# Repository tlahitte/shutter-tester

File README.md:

# Shutter Tester

> **Rev B (this fork).** A redesign that arrives fully assembled from JLCPCB with no
> soldering: a sensor board (ESP32-C6, three photodiodes, USB-C) and a separate light
> board. One set of both boards is roughly £70 to £85 delivered to the UK. Design,
> cost breakdown and ordering steps are in [hardware/README.md](hardware/README.md),
> firmware in [firmware/shutter-tester-revb](firmware/shutter-tester-revb). Not yet built
> or tested on hardware. The web UI also includes the USB (Web Serial) connection from
> [9vvin's fork](https://github.com/9vvin/shutter-tester) and the theming, error
> reporting and list fixes from [MichalTorma's fork](https://github.com/MichalTorma/shutter-tester).
> Everything below is Ben Pirt's original README for the original
> board, which this work is based on.

A low cost but capable three-point shutter speed tester that runs on ESP32. It uses the PCB design to provide the physical structure of the tester so that all you need to do is solder it together and all of the mechanical design is taken care of.
It runs on ESP32 so is easily updated using the Arduino platform. The project is 100% open source (see the [license file](LICENSE.md) for details).
The UI runs in the browser and communicates with the shutter tester via Bluetooth - you can try out the UI [here](https://bjpirt.github.io/shutter-tester/?demo=true).

## Design

The design of the shutter tester is quite simple; it uses three IS485E / IS486E light sensors with built-in amplifiers to trigger three digital input interrupts on the ESP32 MCU. I wanted to keep the front side of the PCB clear to avoid it ever scratching the camera body so have opted for using surface mount components. I've used quite large packages for these so that they can be more easily hand soldered. The ESP32 uses an "ESP32 C3 Super Mini" module which is very small, can be surface mounted and has USB C built-in which can be used to power the whole board. I've kept the PCB size down to 50mm so that you can take advantage of low cost PCB fabrication. There are silk-screen markings to help position the tester over the camera shutter and three large holes to help see the edges from behind. It should either be taped in place or held with an elastic band.

The sensor has a Bluetooth connection and you can connect this to Chrome to use quite a capable web interface so you can get a lot of detail on the calibration. You can try out the UI [here](https://bjpirt.github.io/shutter-tester/?demo=true)

## Bill of materials

The BoM is quite low cost and relatively minimal:

- 1 x ESP32 C3 Super Mini module
- 3 x IS485E light sensor
- 6 x 1k 1206 SMD Resistor
- 3 x 2k 1206 SMD Resistor
- 3 x 0.01uF 1206 SMD Capacitor

## Assembly

The main thing to take care over during assembly is to ensure the lens of the light sensor aligns to the small hole in the PCB that allows the light through. The three legs of the sensor should be bent down slightly so that they can solder onto the three pads on the PCB.

The capacitors and resistors can be easily hand soldered (a finer soldering iron tip helps here) by applying solder to one of the pads on the PCB, using tweezers, solder one end of the component to the soldered pad on the PCB, then solder the other end once it is held in place. If you're experienced in surface mounting you could always use solder paste, but it's pretty straightforward without this. There are markings on the board for which component goes where (C1, C2 and C3 for the capacitors, Resistor values are marked 1k and 2k). The capacitors are optional and may be removed in a future iteration.

It's best to test the ESP32 module before soldering to ensure it's working fine. Program this using the sketch included and make sure it is outputting "Ready to measure" on the serial console (running at 921600 baud).

It's a good idea to place some black insulation tape over the back of the sensors otherwise stray light can cause false readings.

## Usage

Attach the shutter tester behind the shutter of the camera (I normally use 2 - 3 small blobs of Blu-Tak which works well). You can use the three larger holes in the tester to align with the edges of the shutter aperture. Open the shutter once you've this so you can check it's properly positioned by setting the shutter to "Bulb" and opening it. Remove the lens (if possible) and place a strong, even light at the front of the camera. You can use a full size bulb for this so long as it is the type that has a white diffuser bulb, not clear. Basically you want to ensure that light can pass directly through the three holes to reach the sensors, not at an angle. I've also had good results with a small USB powered LED panel.

### Using Bluetooth

There is a user interface that connects to the ESP32 from a Chrome web browser directly and lets you analyse all of the measurements quite easily.

You can easily use the [latest version](https://bjpirt.github.io/shutter-tester/). You should then be able to click the `Connect` button and pair with your shutter tester using Bluetooth. Select the speed you want to test, set up the light and fire the shutter. The new reading should appear in the table.

If you want to just try out the UI without a tester, you can use [this link](https://bjpirt.github.io/shutter-tester/?demo=true) and the "Test" button will simulate a shutter being fired. From a privacy perspective, the UI runs entirely in your browser and nothing goes over the internet.

If you want to run this locally you can do the following:

- Install Node.js (v22)
- Open a terminal in the `ui` folder of this repository
- run `npm install`
- run `npm run dev`
- Go to the URL printed in your terminal ([http://localhost:5173/](http://localhost:5173/))

### Using serial

Open a serial terminal to the ESP32 (this is built in to the Arduino IDE). You'll need to connect at 921600 baud.

Fire the shutter and it will print out the timings to the serial console. There are two sets of timings:

- The time taken for each shutter to travel across the frame - it's important to try and get both shutters moving at around the same speed
- The time each sensor was exposed for in microseconds, milliseconds and fractions of a second

```
Ready to measure

Shutter timing
Shutter 1: 1-2: 16582 uS || 2-3: 12632 uS
Shutter 2: 1-2: 23756 uS || 2-3: 18462 uS

Exposure timing
Sensor 1: 4346 uS || 4.3 mS || 1 / 228
Sensor 2: 5028 uS || 5.0 mS || 1 / 198
Sensor 3: 5528 uS || 5.5 mS || 1 / 182
```

In this example, the time taken for the first shutter to travel between the first and second (centre) sensors was 16582 microseconds and 12632 microseconds between the second (centre) and third sensor. You can see that in this example the second shutter is slow and would need adjusting.

Looking at the exposure time at each sensor, you can see the timings would need adjusting to give a good even exposure. First you would adjust the shutter timings to try and get them similar and then adjust both shutter tensioners to get the exposure time to match the expected (in this case it should have been 1/250 S)

# To Do

- [ ] Calculate variations across shutter and whether they are within tolerances
- [ ] Add graph visualisation of shutter speeds
- [ ] Generate report from three point test
- [x] Enable detailed measurements to be shown / hidden in three point mode
- [x] Deploy to GitHub pages using GitHub actions
- [x] Automatically work out vertical or horizontal shutter
- [x] Display full shutter timing
- [x] Separate shutter timing mode
- [x] Single shot mode (only show last shot timing) - useful for initial tuning
- [x] Compensation for sensor width

## Future

- [ ] Add persistence in the browser to enable common presets to be stored - e.g. camera types with speeds
- [ ] Enable different "runs" to be stored and compared so you can see progression when adjusting
- [ ] Add exposure measurement with light to frequency sensor
- [ ] Investigate reflective measurement from front of camera for e.g. Barnack Leicas
- [ ] Investigate using an analog photodiode instead of a binary sensor

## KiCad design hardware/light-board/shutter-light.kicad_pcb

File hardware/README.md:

# Shutter tester rev B hardware

Derived from Ben Pirt's three-point shutter tester
(https://github.com/bjpirt/shutter-tester), hardware under CERN-OHL-P v2. The upstream
KiCad 8 board is still here as `shutter-tester.kicad_*` for reference.

Rev B is two 2-layer boards that arrive fully assembled: a 77 x 34 mm sensor board and a
50 x 50 mm light board. Nothing to solder.

| Board | Folder | What it does |
|-------|--------|--------------|
| Sensor | `sensor-board/` | Sits at the film plane. Three photodiodes on the frame diagonal, ESP32-C6, USB-C |
| Light | `light-board/` | Nine white LEDs, DC driven from any USB-C charger, goes in front of the lens |

## Sensor board

- 3 x Vishay VBPW34SR photodiodes mounted on the component side, each looking through a
  1.2 mm plated hole. The camera-facing side is flat with no parts on it.
- Each photodiode feeds a transimpedance amp (MCP6004, 1M, about 23 kHz bandwidth) and
  an LM339 comparator. The firmware sets each comparator threshold with a filtered PWM
  output, so calibration is automatic and there are no trimmers.
- ESP32-C6-WROOM-1-N8 timestamps comparator edges in hardware (MCPWM capture), so timing
  does not depend on interrupt latency.
- USB-C for power, flashing and serial. BOOT button for manual download mode if needed.
- The board is 34 mm tall so it drops into the film channel and lies on the film rails.
  The frame centre is 25 mm from the USB end, so the plug lies in the channel on one
  side of the gate. The electronics reach 52 mm the other way and sit over the cassette
  chamber. That fits the film cavity of a normal 35 mm SLR or rangefinder; it is too long
  for a compact, where it has to be held against the back instead.
- Sensor positions on the board: (9,7), (25,17), (41,27) mm. Silk on the camera side
  shows the 36 x 24 mm frame outline.

## Light board

9 LEDs at about 21 mA each, straight from USB 5 V through 100R. No PWM anywhere, so the
light has no flicker that could be read as a shutter edge. Four 3.2 mm mounting holes.
If the sensor board reports saturation, move the light further away.

## Light levels

Estimates only, nothing measured. A photodiode behind a 1.2 mm aperture gives roughly
1.3 mV per lux of white LED light at the amplifier output, and the output clips at about
1.6 V. With the light board held against the front of the lens that works out to:

| Lens setting | Centre sensor | Corner sensors |
|--------------|--------------:|---------------:|
| f/2          | clips, move the light back | about 1 V |
| f/2.8        | about 1.2 V   | about 0.5 V |
| f/5.6        | about 0.3 V   | about 0.12 V |
| f/8          | about 0.15 V  | about 0.06 V |

So test with the lens between f/2.8 and f/8. Calibration needs at least 30 mV between dark
and lit and warns below 60 mV. With the lens off, start with the light 20 cm away. If the
firmware reports saturation, move the light back; if it reports too dim, open the lens up.

## Regenerating

The KiCad files are generated. Change the Python, not the KiCad files.

    . scripts/_env.sh sensor-board
    (cd hardware/gen && "$KICAD_PY" sensor_board.py)    # or light_board.py
    scripts/check.sh sensor-board                       # ERC + DRC, must be clean
    scripts/render.sh sensor-board front                # PNG in fab/sensor-board/
    scripts/fab.sh sensor-board                         # fab/sensor-board/jlcpcb/

`fab.sh` ends by running `scripts/cplcheck.py`. It downloads JLCPCB's own footprint for
every LCSC part on the BOM, lays it on the board at the position and rotation written in
`cpl.csv`, and fails if a pad misses or a diode or IC ends up the wrong way round. The
rotation and origin corrections it checks live in the `FIX` table in `fab.sh`.

## Estimated cost

Estimate from 16 Nov 2026, in USD because that is what JLCPCB quotes in. Part prices are
live JLCPCB prices on that date. The fees are JLCPCB's usual economic assembly fees and
are not taken from a real quote, so treat the totals as a guide and check the quote page.

| Per order | Sensor board | Light board |
|-----------|-------------:|------------:|
| 5 bare PCBs (minimum) | $2 | $2 |
| Assembly setup + stencil | $9.50 | $9.50 |
| Extended parts fee ($3 per part type) | $15 (5 types) | $6 (2 types) |
| Parts, per assembled board | $7.30 | $0.34 |
| **Total, 2 boards assembled** | **about $42** | **about $19** |
| **Total, 5 boards assembled** | **about $64** | **about $20** |

One working set (2 of each, the minimum JLCPCB will assemble) comes to about $60 before
shipping. Add roughly $15 to $25 shipping to the UK and 20% VAT at checkout, so expect
somewhere around £70 to £85 delivered. Most of the cost is fixed fees, which is why a
single set is expensive per board and five sets are only about £100.

## Ordering at JLCPCB

Two separate orders, one per board. For each one:

1. jlcpcb.com, "Order now", upload `fab/<board>/jlcpcb/gerbers.zip`.
2. PCB options: 2 layers, 1.6 mm, qty 5, HASL lead-free. Black solder mask for the sensor
   board (less stray light), any colour for the light board. Leave the rest at default.
3. Turn on "PCB Assembly": Economic, Top side, qty 2 or 5, "Confirm parts placement" on.
4. Upload `bom.csv` and `cpl.csv`. Every part should match by LCSC number. If one is out
   of stock, stop and pick a substitute before going further.
5. In the placement preview, check before paying. `cplcheck.py` has already compared
   every placement with JLCPCB's footprints, so anything that looks wrong here is worth
   stopping for:
   - U2, U3 (SOIC-14): pin 1 dot matches the silk dot
   - U4 (SOT-223): tab on the wide pad
   - U1 (ESP32 module): antenna end at the board edge, over the bare area
   - J1 (USB-C): opening faces off the board and the two pegs sit in their holes
   - Sensor board LED1, LED2: cathode mark matches the silk
   - Light board D1 to D9: the large pad of the LED sits on the large board pad (the
     cathode, on the left)
   - D1 to D3 on the sensor board: body centred over the hole (either way round is fine,
     the circuit does not care about photodiode polarity)
6. Ship to the UK. Under £135, VAT is collected at checkout and there is nothing to pay
   on delivery.

## Not verified yet

- No board has been built. The front end gain is an estimate and the firmware has only
  been compiled, never run on hardware.
- The corrections written into `cpl.csv` (SOT-223 +180, SOIC +270, 2835 LED +180, USB-C
  origin moved 1.394 mm towards its pads) were worked out from JLCPCB's EasyEDA footprints
  for the exact parts and are checked by `cplcheck.py`. That assumes JLCPCB places parts the
  way its footprint is drawn, which is how it normally works but has not been confirmed
  with a real order, hence step 5.
- The photodiodes are clear packages on the open side of the board, so room light reaches
  them from behind, and the two 2.5 mm sighting holes let light straight through. Expect to
  need black tape over D1 to D3 and over both sighting holes, or a dim room.
- Fit in a real camera has not been tried. Cut a 77 x 34 mm piece of card, mark the frame
  centre 25 mm from one end, and check it lies on the film rails of your camera with room
  for a USB-C plug on the short end before ordering.
- VBPW34SR stock at JLCPCB was 925 on 16 Nov 2026. It dropped to 10 in June 2026 and was
  restocked within a month, so recheck before ordering. There is no drop-in alternative.
- Bluetooth range with the board against a metal camera body is unknown. The antenna is
  at the far end over the cassette chamber. If Bluetooth is weak, use the USB connection
  in the web UI.
- Black solder mask at 1.6 mm with HASL is listed by JLCPCB as an economic assembly
  option. If the order page refuses it, pick green and plan on the black tape below.
- The four USB shell legs have solder paste in their slots so they are reflowed with the
  other parts. If the placement preview or the delivered board shows them unsoldered, the
  connector is held by its pins only: support the cable and do not lever on the plug.
- Coupling from the USB data lines and comparator outputs into the 1M amplifier inputs is
  kept down by extra spacing, but is an estimate, not a measurement. If a channel shows
  spurious edges at very low light, use Bluetooth instead of USB for that test.
- No ESD protection or fuse on USB. Fine for a bench prototype.

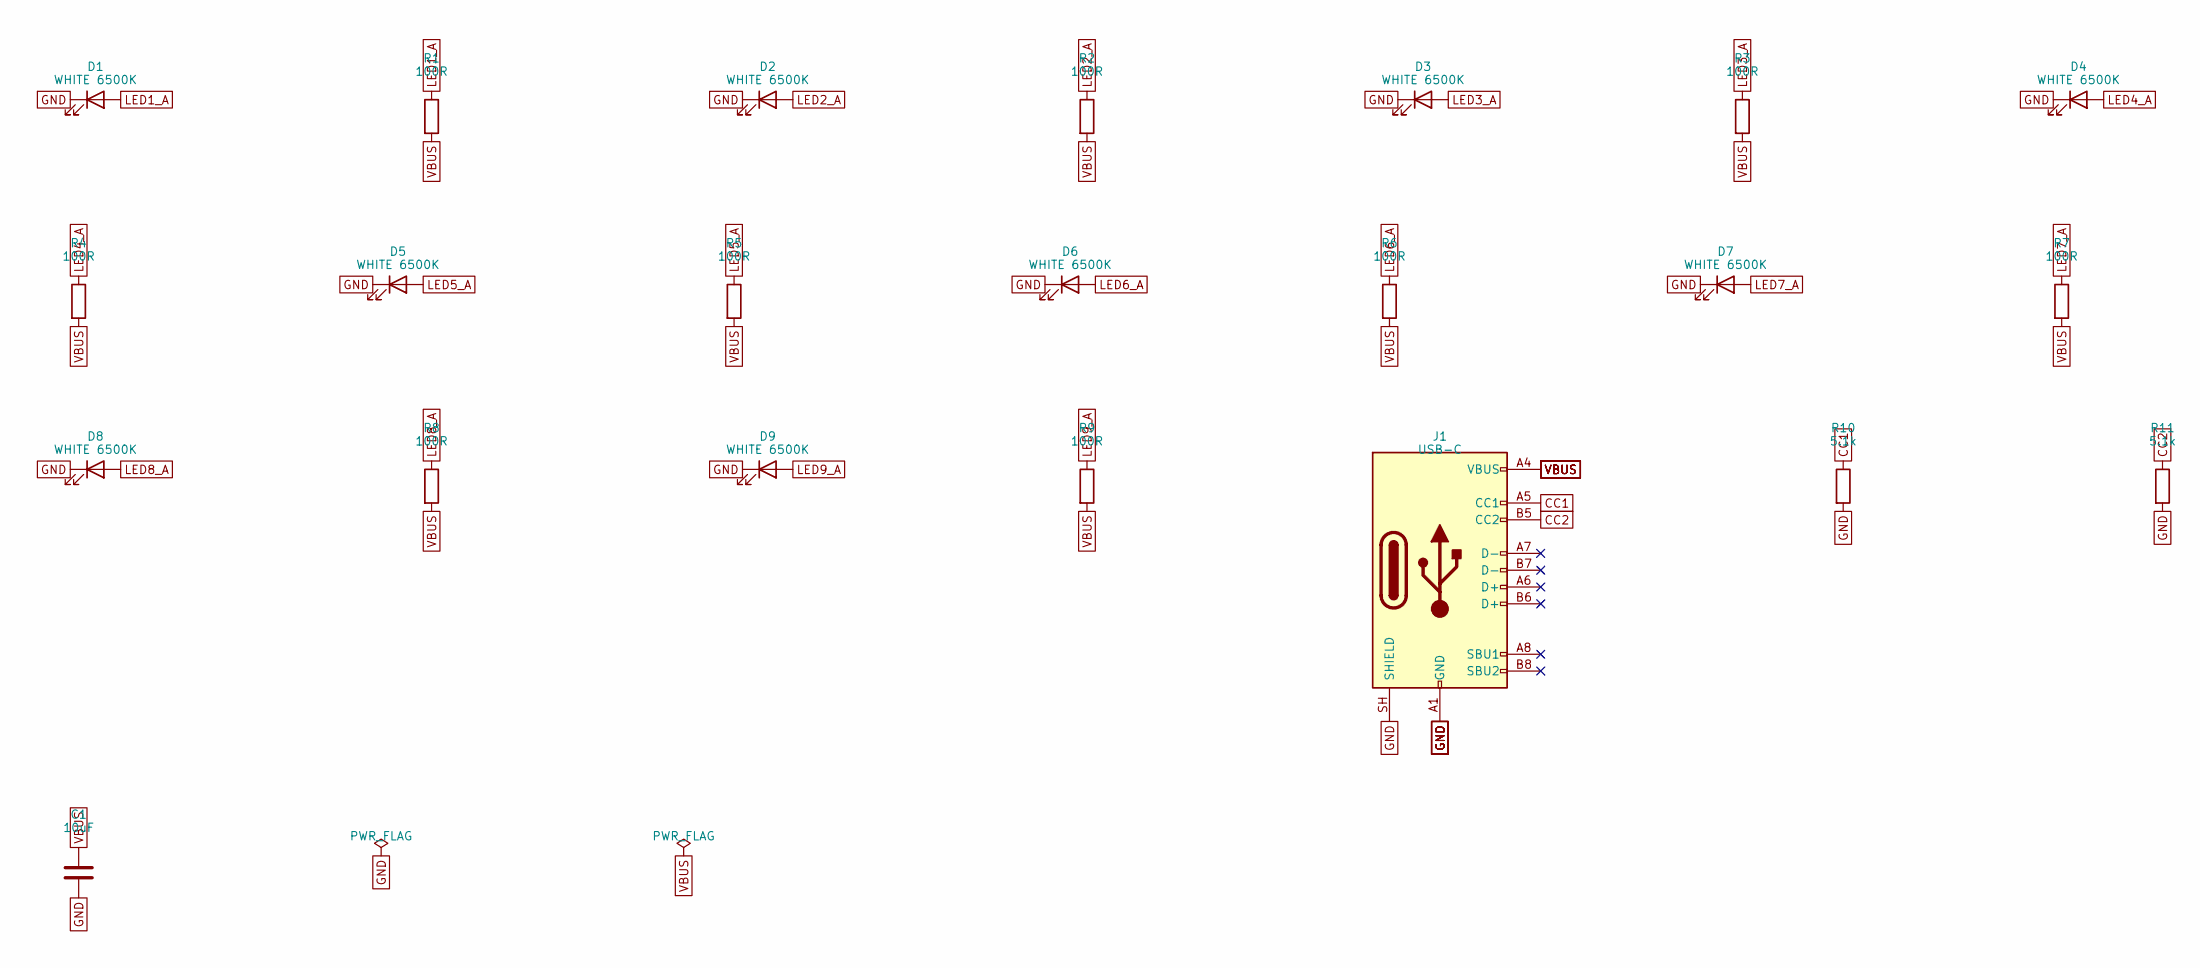
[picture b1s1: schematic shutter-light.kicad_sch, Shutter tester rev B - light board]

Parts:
C1: 10uF; C_0805_2012Metric; LCSC C15850
D1, D2, D3, D4, D5, D6, D7, D8, D9: WHITE 6500K; LED_PLCC_2835; MPN 67-21S/KK7C-H657034Z15/DT; LCSC C385305
J1: USB-C; USB_C_Receptacle_HRO_TYPE-C-31-M-12; MPN TYPE-C-31-M-12; LCSC C165948
R1, R2, R3, R4, R5, R6, R7, R8, R9: 100R; R_0805_2012Metric; LCSC C17408
R10, R11: 5.1k; R_0402_1005Metric; LCSC C25905

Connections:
CC1: J1.A5 (CC1), R10.1
CC2: J1.B5 (CC2), R11.1
GND: C1.2, D1.1 (K), D2.1 (K), D3.1 (K), D4.1 (K), D5.1 (K), D6.1 (K), D7.1 (K), D8.1 (K), D9.1 (K), J1.A1 (GND), J1.A12 (GND), J1.B1 (GND), J1.B12 (GND), J1.SH (SHIELD), R10.2, R11.2
LED1_A: D1.2 (A), R1.1
LED2_A: D2.2 (A), R2.1
LED3_A: D3.2 (A), R3.1
LED4_A: D4.2 (A), R4.1
LED5_A: D5.2 (A), R5.1
LED6_A: D6.2 (A), R6.1
LED7_A: D7.2 (A), R7.1
LED8_A: D8.2 (A), R8.1
LED9_A: D9.2 (A), R9.1
VBUS: C1.1, J1.A4 (VBUS), J1.A9 (VBUS), J1.B4 (VBUS), J1.B9 (VBUS), R1.2, R2.2, R3.2, R4.2, R5.2, R6.2, R7.2, R8.2, R9.2

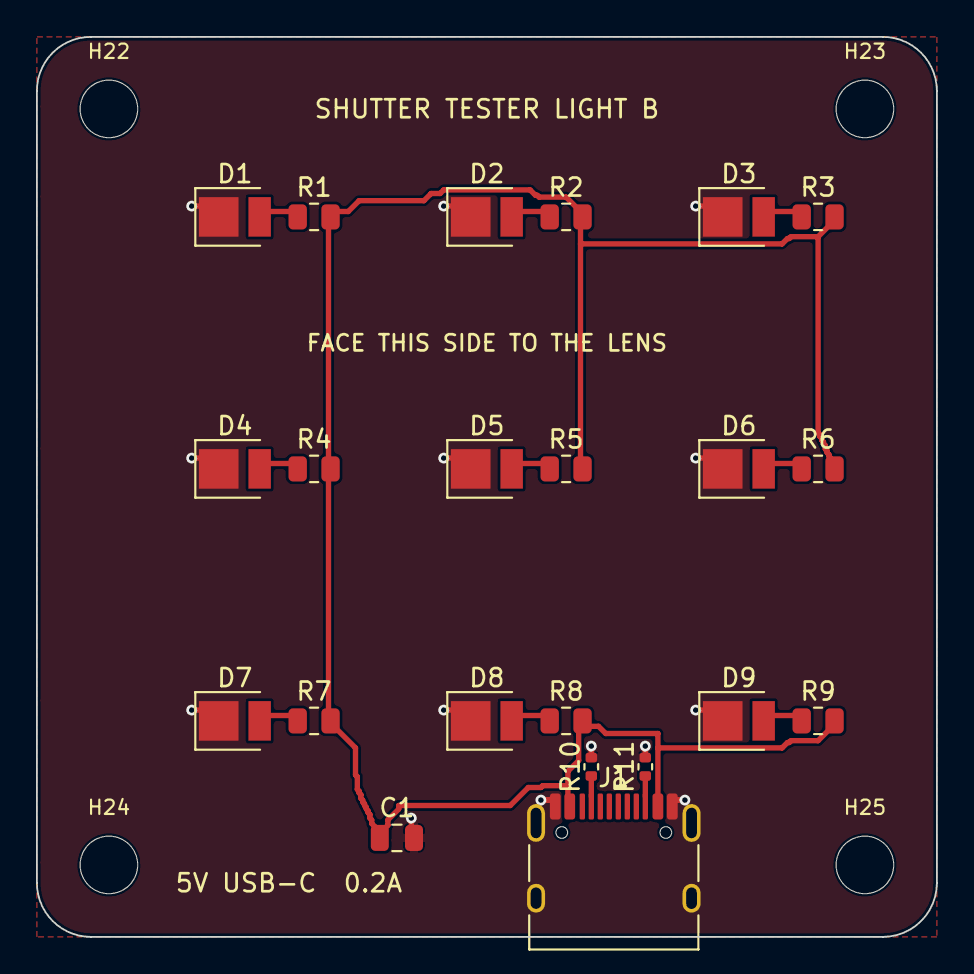
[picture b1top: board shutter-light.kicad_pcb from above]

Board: 2 copper layers, 50.0 x 50.0 mm, 26 parts (0 on the bottom side), 13 nets.

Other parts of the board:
H22, H23, H24, H25: NPTH_3.2mm

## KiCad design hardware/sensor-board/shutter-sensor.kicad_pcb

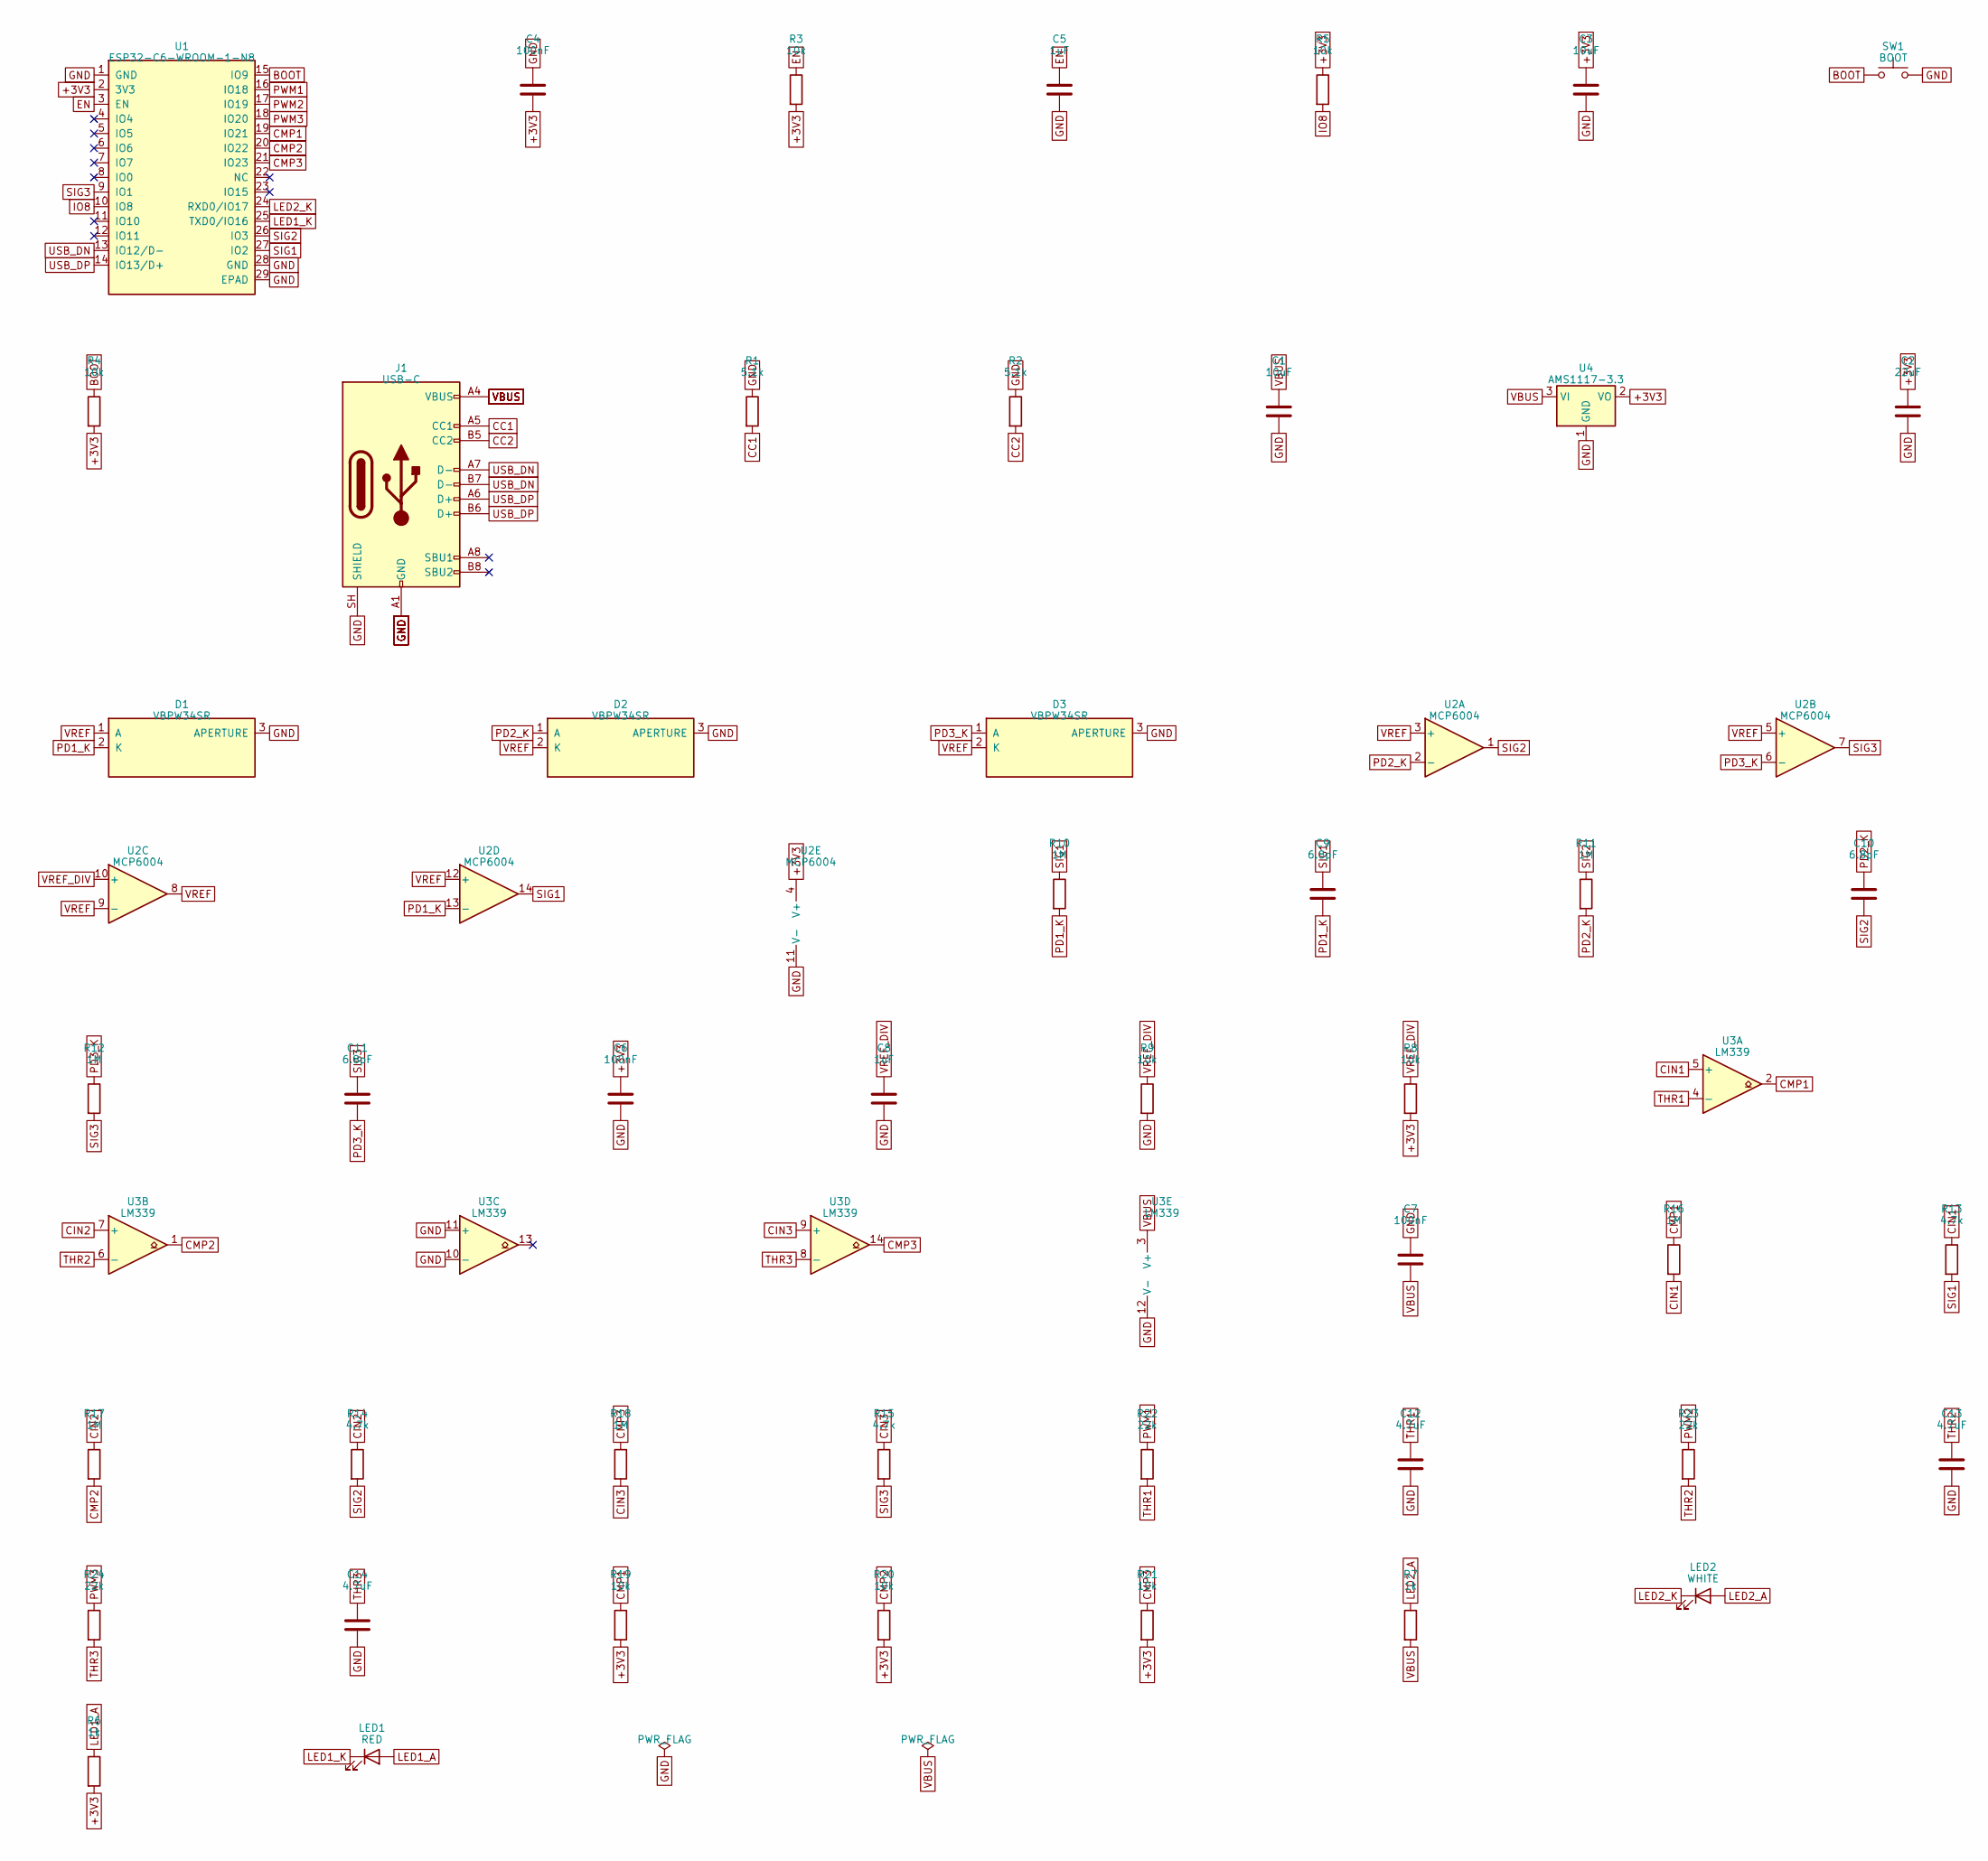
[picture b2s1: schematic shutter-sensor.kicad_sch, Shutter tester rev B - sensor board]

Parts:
C1, C3: 10uF; C_0805_2012Metric; LCSC C15850
C2: 22uF; C_0805_2012Metric; LCSC C45783
C4, C6, C7: 100nF; C_0402_1005Metric; LCSC C1525
C5, C8: 1uF; C_0402_1005Metric; LCSC C52923
C9, C10, C11: 6.8pF; C_0402_1005Metric; LCSC C1576
C12, C13, C14: 4.7uF; C_0603_1608Metric; LCSC C19666
D1, D2, D3: VBPW34SR; VBPW34SR_Aperture; MPN VBPW34SR; LCSC C845527
J1: USB-C; USB_C_Receptacle_HRO_TYPE-C-31-M-12; MPN TYPE-C-31-M-12; LCSC C165948
LED1: RED; LED_0603_1608Metric; MPN KT-0603R; LCSC C2286
LED2: WHITE; LED_0603_1608Metric; MPN KT-0603W; LCSC C2290
R1, R2: 5.1k; R_0402_1005Metric; LCSC C25905
R3, R4, R5, R8, R9, R19, R20, R21: 10k; R_0402_1005Metric; LCSC C25744
R6, R7: 1k; R_0402_1005Metric; LCSC C11702
R10, R11, R12, R16, R17, R18: 1M; R_0402_1005Metric; LCSC C26083
R13, R14, R15: 4.7k; R_0402_1005Metric; LCSC C25900
R22, R23, R24: 22k; R_0402_1005Metric; LCSC C25768
SW1: BOOT; SW_Push_1P1T_XKB_TS-1187A; MPN TS-1187A-B-A-B; LCSC C318884
U1: ESP32-C6-WROOM-1-N8; ESP32-C6-WROOM-1; MPN ESP32-C6-WROOM-1-N8; LCSC C5366877
U2: MCP6004; SOIC-14_3.9x8.7mm_P1.27mm; MPN MCP6004T-I/SL; LCSC C7378
U3: LM339; SOIC-14_3.9x8.7mm_P1.27mm; MPN LM339DT; LCSC C71036
U4: AMS1117-3.3; SOT-223-3_TabPin2; MPN AMS1117-3.3; LCSC C6186

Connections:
+3V3: C2.1, C3.1, C4.2, C6.1, R3.2, R4.2, R5.1, R6.2, R8.2, R19.2, R20.2, R21.2, U1.2 (3V3), U2.4 (V+), U4.2 (VO)
BOOT: R4.1, SW1.1, U1.15 (IO9)
CC1: J1.A5 (CC1), R1.2
CC2: J1.B5 (CC2), R2.2
CIN1: R13.1, R16.2, U3.5 (+)
CIN2: R14.1, R17.1, U3.7 (+)
CIN3: R15.1, R18.2, U3.9 (+)
CMP1: R16.1, R19.1, U1.19 (IO21), U3.2
CMP2: R17.2, R20.1, U1.20 (IO22), U3.1
CMP3: R18.1, R21.1, U1.21 (IO23), U3.14
EN: C5.1, R3.1, U1.3 (EN)
GND: C1.2, C2.2, C3.2, C4.1, C5.2, C6.2, C7.1, C8.2, C12.2, C13.2, C14.2, D1.3 (APERTURE), D2.3 (APERTURE), D3.3 (APERTURE), J1.A1 (GND), J1.A12 (GND), J1.B1 (GND), J1.B12 (GND), J1.SH (SHIELD), R1.1, R2.1, R9.2, SW1.2, U1.1 (GND), U1.28 (GND), U1.29 (EPAD), U2.11 (V-), U3.10 (-), U3.11 (+), U3.12 (V-), U4.1 (GND)
IO8: R5.2, U1.10 (IO8)
LED1_A: LED1.2 (A), R6.1
LED1_K: LED1.1 (K), U1.25 (TXD0/IO16)
LED2_A: LED2.2 (A), R7.1
LED2_K: LED2.1 (K), U1.24 (RXD0/IO17)
PD1_K: C9.2, D1.2 (K), R10.2, U2.13 (-)
PD2_K: C10.1, D2.1 (A), R11.2, U2.2 (-)
PD3_K: C11.2, D3.1 (A), R12.1, U2.6 (-)
PWM1: R22.1, U1.16 (IO18)
PWM2: R23.1, U1.17 (IO19)
PWM3: R24.1, U1.18 (IO20)
SIG1: C9.1, R10.1, R13.2, U1.27 (IO2), U2.14
SIG2: C10.2, R11.1, R14.2, U1.26 (IO3), U2.1
SIG3: C11.1, R12.2, R15.2, U1.9 (IO1), U2.7
THR1: C12.1, R22.2, U3.4 (-)
THR2: C13.1, R23.2, U3.6 (-)
THR3: C14.1, R24.2, U3.8 (-)
USB_DN: J1.A7 (D-), J1.B7 (D-), U1.13 (IO12/D-)
USB_DP: J1.A6 (D+), J1.B6 (D+), U1.14 (IO13/D+)
VBUS: C1.1, C7.2, J1.A4 (VBUS), J1.A9 (VBUS), J1.B4 (VBUS), J1.B9 (VBUS), R7.2, U3.3 (V+), U4.3 (VI)
VREF: D1.1 (A), D2.2 (K), D3.2 (K), U2.3 (+), U2.5 (+), U2.8, U2.9 (-), U2.12 (+)
VREF_DIV: C8.1, R8.1, R9.1, U2.10 (+)

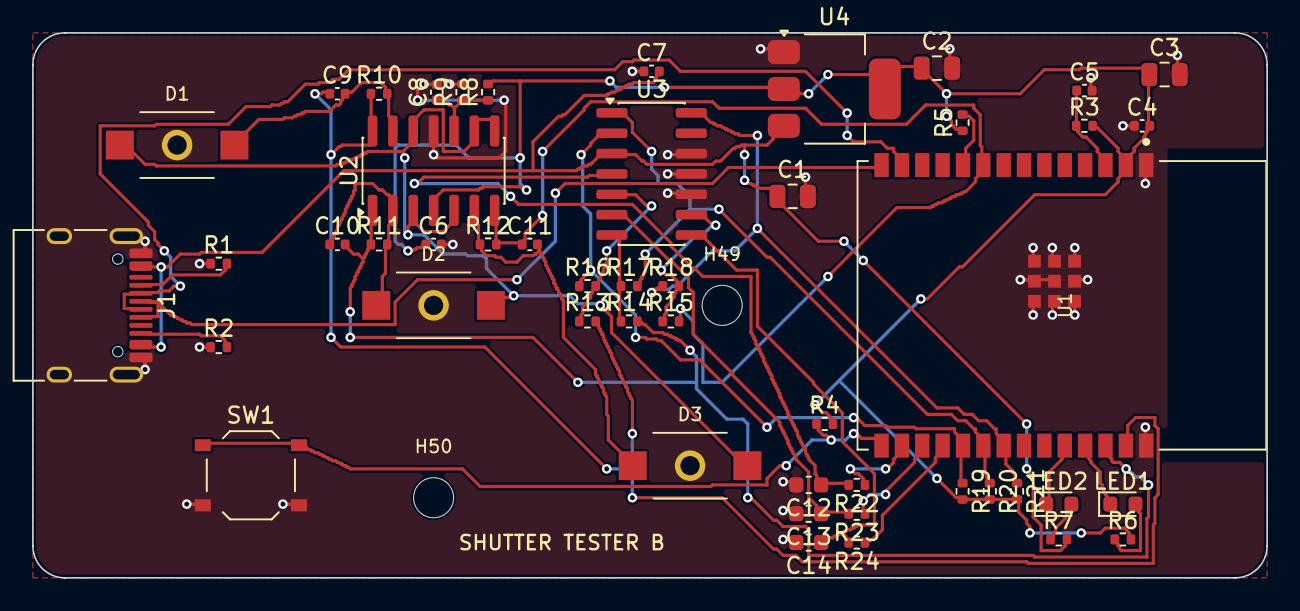
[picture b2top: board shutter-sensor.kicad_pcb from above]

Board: 2 copper layers, 77.0 x 34.0 mm, 51 parts (0 on the bottom side), 34 nets.

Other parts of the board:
H49, H50: NPTH_2.5mm

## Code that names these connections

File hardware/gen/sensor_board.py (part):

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# Frame centre is (25, 17); sensors sit on the frame diagonal, 16 mm and 10 mm off centre.
PDXY = ((9.0, 7.0), (25.0, 17.0), (41.0, 27.0))
PD = dict(sym='shutter:VBPW34SR', fp='shutter:VBPW34SR_Aperture', lcsc='C845527', mpn='VBPW34SR')
d.add('D1', 'VBPW34SR', PD['sym'], PD['fp'], {'1': 'VREF', '2': 'PD1_K', '3': 'GND'}, PDXY[0], 0, lcsc=PD['lcsc'], mpn=PD['mpn'])
d.add('D2', 'VBPW34SR', PD['sym'], PD['fp'], {'1': 'PD2_K', '2': 'VREF', '3': 'GND'}, PDXY[1], 0, lcsc=PD['lcsc'], mpn=PD['mpn'])
d.add('D3', 'VBPW34SR', PD['sym'], PD['fp'], {'1': 'PD3_K', '2': 'VREF', '3': 'GND'}, PDXY[2], 0, lcsc=PD['lcsc'], mpn=PD['mpn'])
UX, UY = 25.0, 8.6
d.add('U2', 'MCP6004', 'Amplifier_Operational:MCP6004', 'Package_SO:SOIC-14_3.9x8.7mm_P1.27mm',
      {'1': 'SIG2', '2': 'PD2_K', '3': 'VREF', '4': '+3V3', '5': 'VREF', '6': 'PD3_K', '7': 'SIG3',
       '8': 'VREF', '9': 'VREF', '10': 'VREF_DIV', '11': 'GND', '12': 'VREF', '13': 'PD1_K', '14': 'SIG1'},
      (UX, UY), 90, lcsc='C7378', mpn='MCP6004T-I/SL')
R('R10', '1M', 'SIG1', 'PD1_K', UX - 3.4, UY - 4.8);  C('C9', '6.8pF', 'SIG1', 'PD1_K', UX - 6.0, UY - 4.8)
R('R11', '1M', 'SIG2', 'PD2_K', UX - 3.4, UY + 4.6);  C('C10', '6.8pF', 'PD2_K', 'SIG2', UX - 6.0, UY + 4.6)
R('R12', '1M', 'PD3_K', 'SIG3', UX + 3.4, UY + 4.6);  C('C11', '6.8pF', 'SIG3', 'PD3_K', UX + 6.0, UY + 4.6)
C('C6', '100nF', '+3V3', 'GND', UX, UY + 4.6)
C('C8', '1uF', 'VREF_DIV', 'GND', UX + 0.2, UY - 4.9, 90)
R('R9', '10k', 'VREF_DIV', 'GND', UX + 1.8, UY - 4.9, 90)
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# copper, and nets routed later keep the same distance from them (a USB or comparator edge right
# next to one shows up as a spike on the signal).
RULES = dict(track=0.2, clearance=0.15, via=0.6, drill=0.3, grid=0.1, edge=0.4, corner=2.0, via_pad_gap=0.2,
             guard={'PD1_K': 0.4, 'PD2_K': 0.4, 'PD3_K': 0.4})

if os.environ.get('MAX_RIPS'):
    RULES['max_rips'] = int(os.environ['MAX_RIPS'])
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    root = d.write_schematic()
    d.write_project(RULES)
    # THR2 goes early: its pad on C13 sits between C12 and C14 and gets boxed in otherwise.
    order = ['CC1', 'CC2', 'USB_DN', 'USB_DP', 'PD1_K', 'PD2_K', 'PD3_K', 'THR2', 'THR1', 'THR3']
    # Pads linked to their nearest same-net pad before anything else. The two D- pads and the two
    # D+ pads of J1 interleave, so each pair is joined first (one behind the pins, one in front);
    # otherwise the first trunk walls the other pair in. Pads that fail on an attempt are added.
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

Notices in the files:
hardware/light-board/shutter-light.kicad_sch:
Derived from bjpirt/shutter-tester (CERN-OHL-P)
